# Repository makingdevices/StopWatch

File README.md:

<!-- Improved compatibility of back to top link: See: https://github.com/othneildrew/Best-README-Template/pull/73 -->

<!--
*** Thanks for checking out the Best-README-Template. If you have a suggestion
*** that would make this better, please fork the repo and create a pull request
*** or simply open an issue with the tag "enhancement".
*** Don't forget to give the project a star!
*** Thanks again! Now go create something AMAZING! :D
-->

<!-- PROJECT SHIELDS -->
<!--
*** I'm using markdown "reference style" links for readability.
*** Reference links are enclosed in brackets [ ] instead of parentheses ( ).
*** See the bottom of this document for the declaration of the reference variables
*** for contributors-url, forks-url, etc. This is an optional, concise syntax you may use.
*** https://www.markdownguide.org/basic-syntax/#reference-style-links
-->
[![Instagram][ig-shield]][ig-url]
[![PCBWAY][sponsor-shield]][sponsor-url]
[![Stargazers][stars-shield]][stars-url]
[![Issues][issues-shield]][issues-url]
[![LinkedIn][linkedin-shield]][linkedin-url]

<!-- PROJECT LOGO -->
<br />
<div align="center">

<h3 align="center">Making Devices</h3>

  <p align="center">
    Open Source projects where we struggle with engineering, electronics, coding and who knows what else... In this case, Bytes Counter is a very simple digital tally counter, so hopefully you may find it interesting ;)
  </p>
</div>

<!-- TABLE OF CONTENTS -->
<details>
  <summary>Table of Contents</summary>
  <ol>
    <li>
      <a href="#about-the-project">About The Project</a>
      <ul>
        <li><a href="#built-with">Built With</a></li>
      </ul>
    </li>
    <li>
      <a href="#Build-one">Build one</a>
      <ul>
      </ul>
    </li>
    <li><a href="#usage">Usage</a></li>
    <li><a href="#roadmap">Roadmap</a></li>
    <li><a href="#license">License</a></li>
    <li><a href="#contact">Contact</a></li>
    <li><a href="#Sponsor">Sponsor</a></li>
  </ol>
</details>

<!-- ABOUT THE PROJECT -->
## About The Project

[![Bytes Counter Shot][product-screenshot]](https://makingdevices.com/StopWatch)

This project is a simple StopWatch for measuring times on different processes or activities. The project was chosen to test some 4-layers PCBs and experiment with both the XLP (Extreme Low-Power Technology) and the pic18LF14k50 itself. You can measure from milliseconds to more than 99h. 

The PCB does not have any power button, since the project's approach is to use the XLP technology of the PIC. It only has two buttons: start/mode button and pause/stop button.

<p align="right">(<a href="#readme-top">back to top</a>)</p>

### Built With

[![Microcontroller][PIC]][PIC-url]
[![MPLAB C][MPLAB-C]][MPLAB-C-url]
[![Kicad][kicad-shield]][kicad-url]
[![SPONSOR][sponsor-icon]][sponsor-url]

<p align="right">(<a href="#readme-top">back to top</a>)</p>

<!-- GETTING STARTED -->

## Build one

1. Get the gerber files for the latest version: [V1](https://github.com/makingdevices/StopWatch/blob/main/v1/Gerber/StopWatchV1.zip) 
2. Send them to a PCB manufacturer ([Our Sponsor is PCBWAY][sponsor-url])
3. Buy all the components from the [Bill Of Materials](https://github.com/makingdevices/StopWatch/blob/main/v1/StopWatch_BOM.xlsx)
4. Solder everything with the help of the [schematic](https://github.com/makingdevices/StopWatch/blob/main/v1/schematicv1.pdf)
5. Burn the [latest firmware](https://github.com/makingdevices/StopWatch/blob/main/v1/Simulation/StopWatch.hex)
6. Give us a Star to the respository ;)

Here it is an assembly video:

[![Assembly Shot][YT-screenshot]](https://www.youtube.com/watch?v=HLl4U4vhF9I)

<p align="right">(<a href="#readme-top">back to top</a>)</p>

<!-- USAGE EXAMPLES -->
## Usage

Instructions of use:

- Pressing "Start" will start the StopWatch.
- Pressing "Pause" will stop the StopWatch.
- Long press "Start" : it will change the display mode.
- Long press "Stop" : It will reset the time to 0.
- 60s without pressing any button: Save Energy Mode -> Display off. It will still count the time. 
- 10s without pressing any button in pause mode: Deep Sleep Mode -> Display off. Not counting

<p align="right">(<a href="#readme-top">back to top</a>)</p>

<!-- ROADMAP -->
## Roadmap

- [x] Stopwatch and show it on screen
- [x] enable/disable sound when pressing buttons
- [x] Low Power Consumption
    - [x] Lower the frequency of the microcontroller at minimum
    - [x] Enter deep sleep mode automatically
    - [x] Save energy mode while still working: Display off
- [x] Measure power consumption

See the [open issues](https://github.com/makingdevices/StopWatch/issues) for a full list of proposed features (and known issues).

State: Project <b>FINISHED</b> - 18/08/2022

<p align="right">(<a href="#readme-top">back to top</a>)</p>

<!-- LICENSE -->
## License

## License

Distributed under three licenses:
- [Hardware](/License/HW_cern_ohl_s_v2.pdf)
- [Software](/License/SW_GPLv3.0.txt)
- [Documentation](/License/Documentation_CC-BY-SA-4.0.txt)

[![GPL v3 License][license-shield]][license-url] 
<p align="right">(<a href="#readme-top">back to top</a>)</p>

<!-- CONTACT -->
## Contact

Making Devices - [@MakingDevices](https://www.instagram.com/makingdevices/)

Project Link: [https://github.com/makingdevices/StopWatch](https://github.com/makingdevices/StopWatch)

Other Links: [LinkTree](https://makingdevices.com/links/)

<p align="right">(<a href="#readme-top">back to top</a>)</p>

<!-- Sponsor -->
## Sponsor

PCBWay is the most professional PCB manufacturer for prototyping and low-volume production to work with in the world. With more than a decade in the field, They are committed to meeting the needs of their customers from different industries in terms of quality, delivery, cost-effectiveness and any other demanding requests. As Sponsor of Making Devices, they will be in charge of all the PCBs for MDV, allowing both of us to grow together in a long term partnership. We hope you take them into account for your both personal and professional prototypes or products.

[![Sponsor Shot][sponsor-screenshot-pcb1]][sponsor-url]
[![Sponsor Shot][sponsor-screenshot-pcb1]][sponsor-url]

<p align="right">(<a href="#readme-top">back to top</a>)</p>

<!-- MARKDOWN LINKS & IMAGES -->
<!-- https://www.markdownguide.org/basic-syntax/#reference-style-links -->
[contributors-shield]: https://img.shields.io/github/contributors/makingdevices/StopWatch.svg?style=for-the-badge
[contributors-url]: https://github.com/makingdevices/StopWatch/graphs/contributors
[forks-shield]: https://img.shields.io/github/forks/makingdevices/StopWatch.svg?style=for-the-badge
[forks-url]: https://github.com/makingdevices/StopWatch/network/members
[stars-shield]: https://img.shields.io/github/stars/makingdevices/StopWatch.svg?style=for-the-badge
[stars-url]: https://github.com/makingdevices/StopWatch/stargazers
[issues-shield]: https://img.shields.io/github/issues/makingdevices/StopWatch.svg?style=for-the-badge
[issues-url]: https://github.com/makingdevices/StopWatch/issues
[license-shield]: /images/license.png
[license-url]: https://github.com/makingdevices/StopWatch/tree/main/License
[linkedin-shield]: https://img.shields.io/badge/-LinkedIn-black.svg?style=for-the-badge&logo=linkedin&colorB=555
[linkedin-url]: https://www.linkedin.com/company/making-devices/
[sponsor-shield]: https://img.shields.io/badge/SPONSOR-PCBWAY-black.svg?style=for-the-badge&colorB=1200
[sponsor-url]: https://www.pcbway.com/?from=makingdevices
[sponsor-screenshot-pcb1]: /images/stopwatch_pcb1.jpg
[sponsor-screenshot-pcb2]: /images/stopwatch_pcb2.jpg
[product-screenshot]: images/screenshot.gif
[PIC]: https://img.shields.io/badge/PIC18LF14K50-000000?style=for-the-badge
[PIC-url]: http://ww1.microchip.com/downloads/en/devicedoc/40001350f.pdf
[kicad-shield]: https://img.shields.io/badge/kicad-0b03fc?style=for-the-badge&logo=kicad&logoColor=white
[kicad-url]: https://www.kicad.org/
[YT-screenshot]: images/YT_assembly.PNG
[sponsor-icon]:  https://img.shields.io/badge/-PCBWAY-black.svg?style=for-the-badge&colorB=1200
[ig-shield]: https://img.shields.io/badge/instagram-a83297?style=for-the-badge&logo=instagram&logoColor=white
[ig-url]: https://www.instagram.com/makingdevices/
[MPLAB-C]: https://img.shields.io/badge/MPLAB%20C18-DD0031?style=for-the-badge&logo=C&logoColor=white
[MPLAB-C-url]: https://www.microchip.com/en-us/development-tool/SW006011
[Svelte.dev]: https://img.shields.io/badge/Svelte-4A4A55?style=for-the-badge&logo=svelte&logoColor=FF3E00
[Svelte-url]: https://svelte.dev/
[Laravel.com]: https://img.shields.io/badge/Laravel-FF2D20?style=for-the-badge&logo=laravel&logoColor=white
[Laravel-url]: https://laravel.com
[Bootstrap.com]: https://img.shields.io/badge/Bootstrap-563D7C?style=for-the-badge&logo=bootstrap&logoColor=white
[Bootstrap-url]: https://getbootstrap.com
[JQuery.com]: https://img.shields.io/badge/jQuery-0769AD?style=for-the-badge&logo=jquery&logoColor=white
[JQuery-url]: https://jquery.com

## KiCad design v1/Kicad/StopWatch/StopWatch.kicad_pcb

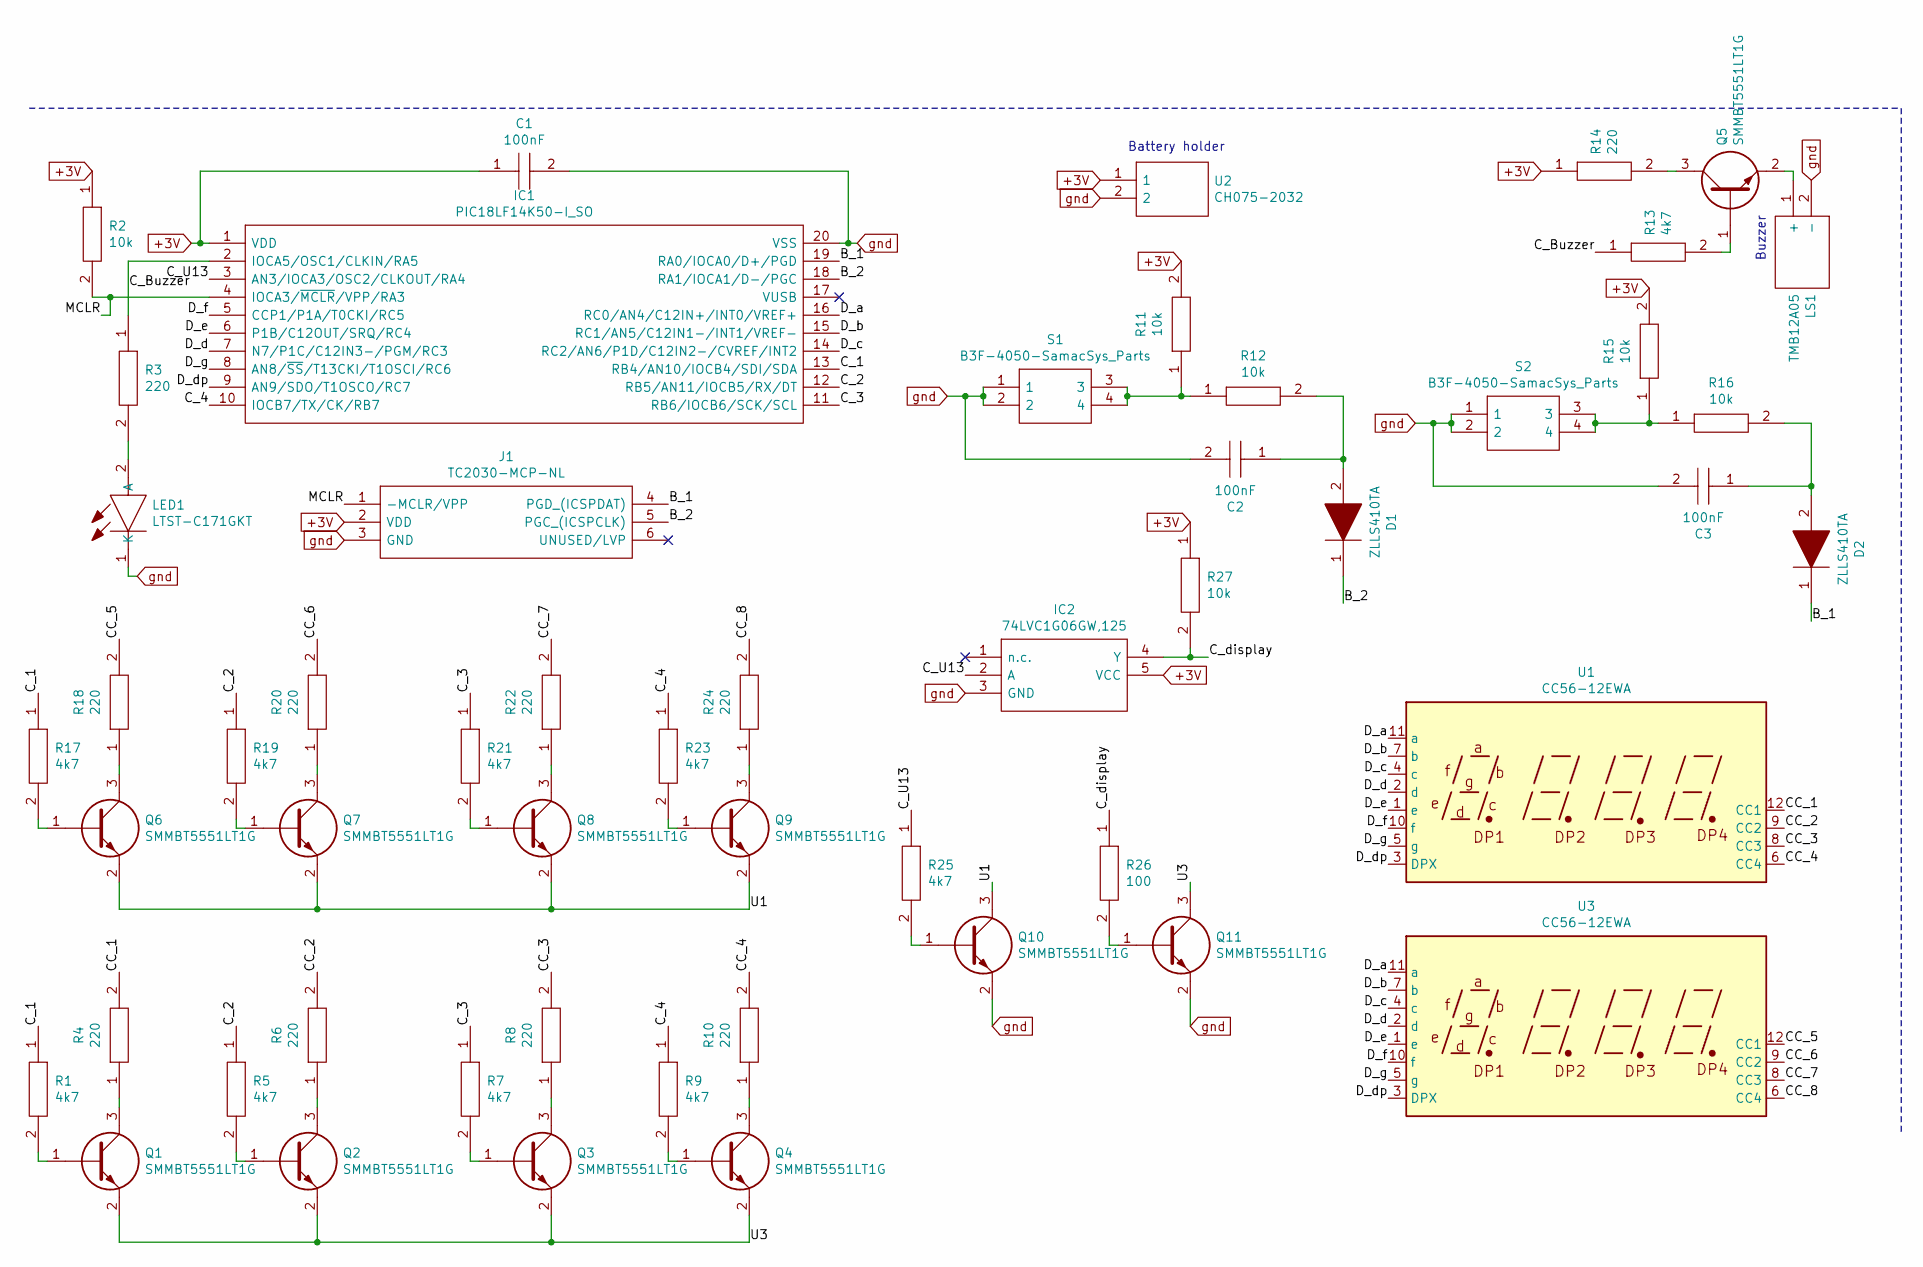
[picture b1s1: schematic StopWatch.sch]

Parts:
C1, C2, C3: 100nF; CAPC2012X145N; Manufacturer_Part_Number GCG21BR71H154KA01K
D1, D2: ZLLS410TA; SOD2513X120N; Manufacturer_Part_Number ZLLS410TA
IC1: PIC18LF14K50-I_SO; SSOP-20_5.3x7.2mm_P0.65mm; Manufacturer_Part_Number PIC18LF14K50-I/SO
IC2: 74LVC1G06GW,125; SOT65P212X110-5N; Manufacturer_Part_Number 74LVC1G06GW,125
J1: TC2030-MCP-NL; Manufacturer_Part_Number TC2030-MCP-NL
LED1: LTST-C171GKT; LEDC2012X90N; Manufacturer_Part_Number LTST-C171GKT
LS1: TMB12A05; Manufacturer_Part_Number TMB12A05
Q1, Q2, Q3, Q4, Q5, Q6, Q7, Q8, Q9, Q10, Q11: SMMBT5551LT1G; SOT96P237X111-3N; Manufacturer_Part_Number SMMBT5551LT1G
R1, R5, R7, R9, R13, R17, R19, R21, R23, R25: 4k7; RESC2012X65N; Manufacturer_Part_Number KTR10EZPF4220
R2, R11, R12, R15, R16, R27: 10k; RESC2012X65N; Manufacturer_Part_Number KTR10EZPF4220
R3, R4, R6, R8, R10, R14, R18, R20, R22, R24: 220; RESC2012X65N; Manufacturer_Part_Number KTR10EZPF4220
R26: 100; RESC2012X65N; Manufacturer_Part_Number KTR10EZPF4220
S1, S2: B3F-4050-SamacSys_Parts; B3F-4000; Manufacturer_Part_Number B3F-4050; Mouser Part Number 653-B3F-4050
U1, U3: CC56-12EWA; CA56-12EWA
U2: CH075-2032; CH0752032; Manufacturer_Part_Number CH075-2032

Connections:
+3V: C1.1, IC1.1 (VDD), IC2.5 (VCC), J1.2 (VDD), R2.1, R11.2, R14.1, R15.2, R27.1, U2.1
/B_1: D2.1, IC1.19 (RA0/IOCA0/D+/PGD), J1.4 (PGD_(ICSPDAT))
/B_2: D1.1, IC1.18 (RA1/IOCA1/D-/PGC), J1.5 (PGC_(ICSPCLK))
/CC_1: R4.2, U1.12 (CC1)
/CC_2: R6.2, U1.9 (CC2)
/CC_3: R8.2, U1.8 (CC3)
/CC_4: R10.2, U1.6 (CC4)
/CC_5: R18.2, U3.12 (CC1)
/CC_6: R20.2, U3.9 (CC2)
/CC_7: R22.2, U3.8 (CC3)
/CC_8: R24.2, U3.6 (CC4)
/C_1: IC1.13 (RB4/AN10/IOCB4/SDI/SDA), R1.1, R17.1
/C_2: IC1.12 (RB5/AN11/IOCB5/RX/DT), R5.1, R19.1
/C_3: IC1.11 (RB6/IOCB6/SCK/SCL), R7.1, R21.1
/C_4: IC1.10 (IOCB7/TX/CK/RB7), R9.1, R23.1
/C_Buzzer: IC1.2 (IOCA5/OSC1/CLKIN/RA5), R3.1, R13.1
/C_U13: IC1.3 (AN3/IOCA3/OSC2/CLKOUT/RA4), IC2.2 (A), R25.1
/C_display: IC2.4 (Y), R26.1, R27.2
/D_a: IC1.16 (RC0/AN4/C12IN+/INT0/VREF+), U1.11 (a), U3.11 (a)
/D_b: IC1.15 (RC1/AN5/C12IN1-/INT1/VREF-), U1.7 (b), U3.7 (b)
/D_c: IC1.14 (RC2/AN6/P1D/C12IN2-/CVREF/INT2), U1.4 (c), U3.4 (c)
/D_d: IC1.7 (N7/P1C/C12IN3-/PGM/RC3), U1.2 (d), U3.2 (d)
/D_dp: IC1.9 (AN9/SDO/T1OSCO/RC7), U1.3 (DPX), U3.3 (DPX)
/D_e: IC1.6 (P1B/C12OUT/SRQ/RC4), U1.1 (e), U3.1 (e)
/D_f: IC1.5 (CCP1/P1A/T0CKI/RC5), U1.10 (f), U3.10 (f)
/D_g: IC1.8 (AN8/~SS~/T13CKI/T1OSCI/RC6), U1.5 (g), U3.5 (g)
/MCLR: IC1.4 (IOCA3/~MCLR~/VPP/RA3), J1.1 (-MCLR/VPP), R2.2
/U1: Q6.2, Q7.2, Q8.2, Q9.2, Q10.3
/U3: Q1.2, Q2.2, Q3.2, Q4.2, Q11.3
unnamed: C2.1, D1.2, R12.2
unnamed: C3.1, D2.2, R16.2
unnamed: LED1.2 (A), R3.2
unnamed: LS1.1 (+), Q5.2
unnamed: Q1.1, R1.2
unnamed: Q1.3, R4.1
unnamed: Q2.1, R5.2
unnamed: Q2.3, R6.1
unnamed: Q3.1, R7.2
unnamed: Q3.3, R8.1
unnamed: Q4.1, R9.2
unnamed: Q4.3, R10.1
unnamed: Q5.1, R13.2
unnamed: Q5.3, R14.2
unnamed: Q6.1, R17.2
unnamed: Q6.3, R18.1
unnamed: Q7.1, R19.2
unnamed: Q7.3, R20.1
unnamed: Q8.1, R21.2
unnamed: Q8.3, R22.1
unnamed: Q9.1, R23.2
unnamed: Q9.3, R24.1
unnamed: Q10.1, R25.2
unnamed: Q11.1, R26.2
unnamed: R11.1, R12.1, S1.3, S1.4
unnamed: R15.1, R16.1, S2.3, S2.4
gnd: C1.2, C2.2, C3.2, IC1.20 (VSS), IC2.3 (GND), J1.3 (GND), LED1.1 (K), LS1.2 (-), Q10.2, Q11.2, S1.1, S1.2, S2.1, S2.2, U2.2

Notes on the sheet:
Battery holder
Buzzer

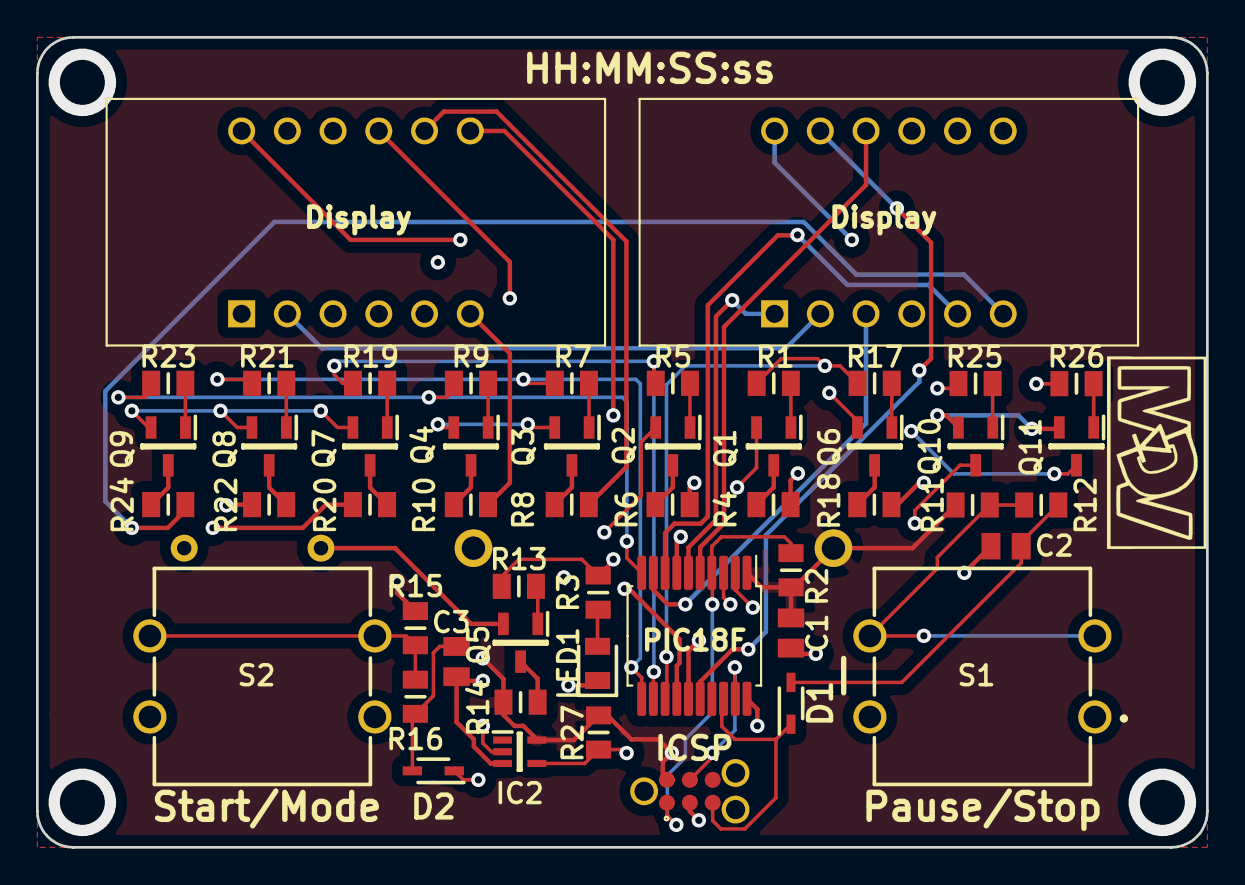
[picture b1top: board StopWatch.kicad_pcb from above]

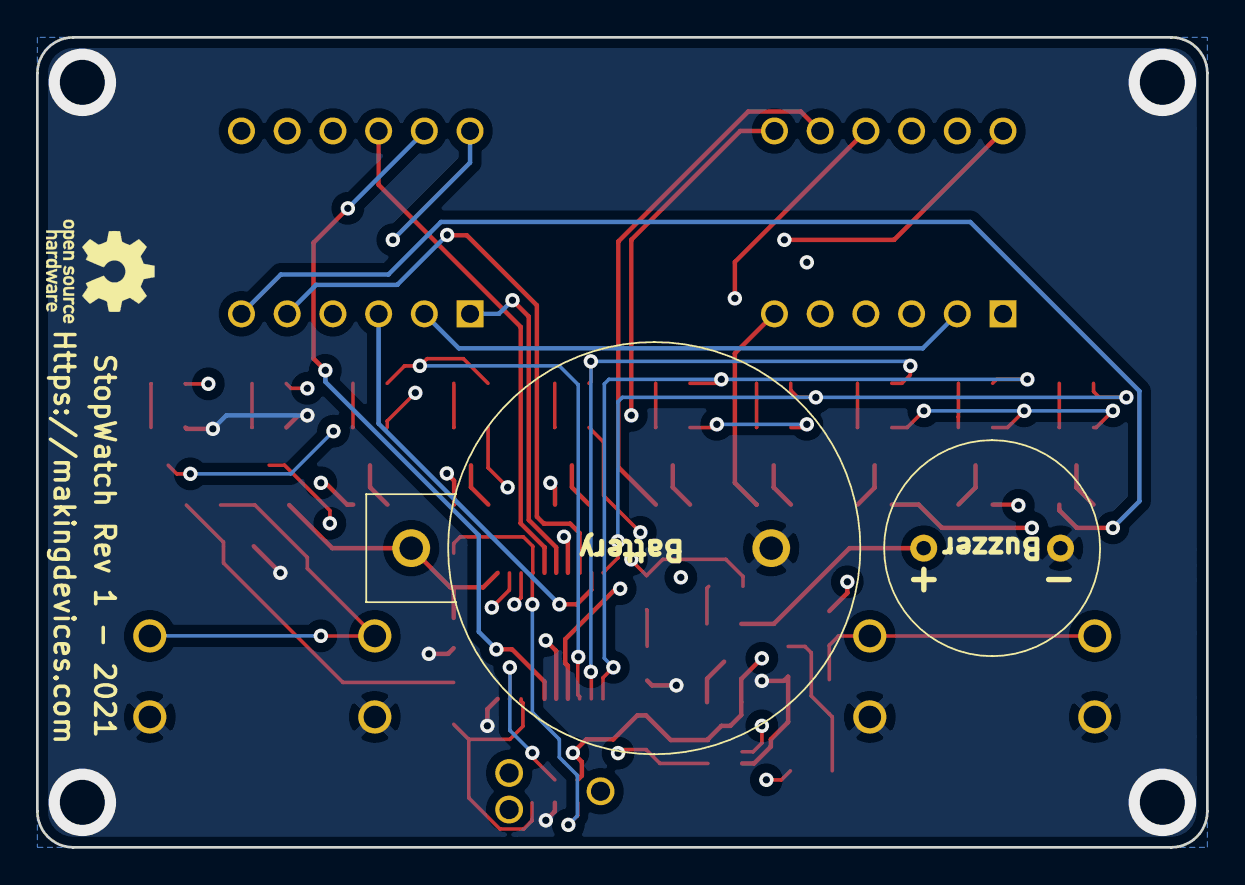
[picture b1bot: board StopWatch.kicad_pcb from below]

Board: 4 copper layers, 65.0 x 45.0 mm, 53 parts (2 on the bottom side), 56 nets.

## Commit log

2022-08-15 Updating files
2022-08-15 readme
2022-08-15 new files
    BOM and Schematic in PDF
2022-12-19 Update root folders
2024-03-24 no message
